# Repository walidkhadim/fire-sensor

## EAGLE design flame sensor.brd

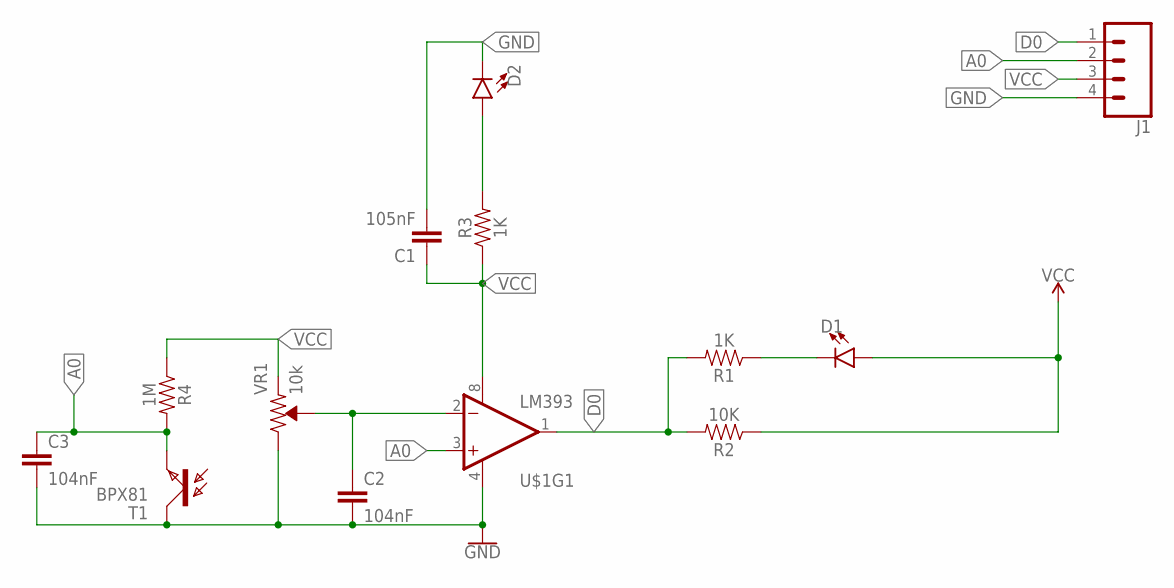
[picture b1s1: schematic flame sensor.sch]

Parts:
C1: 105nF; 1206
C2, C3: 104nF; 1206
D1, D2: LED1206; LED-1206
J1: CONN_04; 1X04
R1, R3: 1K; 0603
R2: 10K; 0603
R4: 1M; 0603
T1: BPX81
U$1: LM393; SO08
VR1: 10k; TRIMPOT-SMD-5MM

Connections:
A0: C3.1, J1.2, R4.2, T1.E, U$1.3 (+IN)
D0: J1.1, R1.2, R2.2, U$1.1 (OUT)
GND: C1.2, C2.2, C3.2, D2.C, J1.4, T1.C, U$1.4 (V-), VR1.C (CW)
unnamed: D1.C, R1.1
unnamed: C2.1, U$1.2 (-IN), VR1.B (WIPER)
unnamed: D2.A, R3.2
VCC: C1.1, D1.A, J1.3, R2.1, R3.1, R4.1, U$1.8 (V+), VR1.A (CCW)

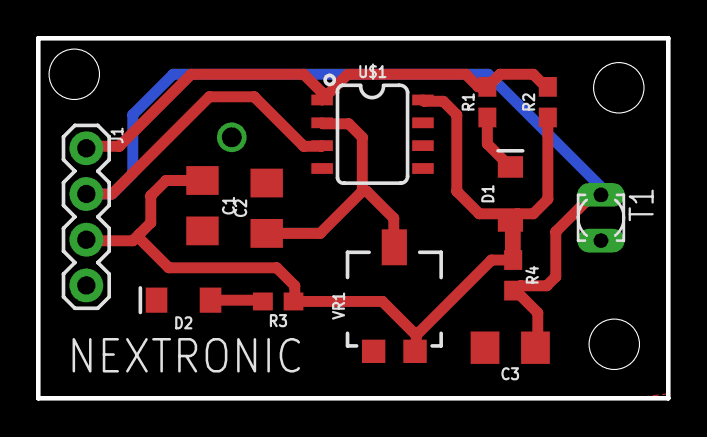
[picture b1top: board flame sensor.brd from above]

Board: 2 copper layers, 35.0 x 20.0 mm, 13 parts (0 on the bottom side), 7 nets.

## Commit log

2017-08-04 schematics

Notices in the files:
parts and their libraries:
SparkFun-Capacitors: Licensing: Creative Commons ShareAlike 4.0 International - https://creativecommons.org/licenses/by-sa/4.0
